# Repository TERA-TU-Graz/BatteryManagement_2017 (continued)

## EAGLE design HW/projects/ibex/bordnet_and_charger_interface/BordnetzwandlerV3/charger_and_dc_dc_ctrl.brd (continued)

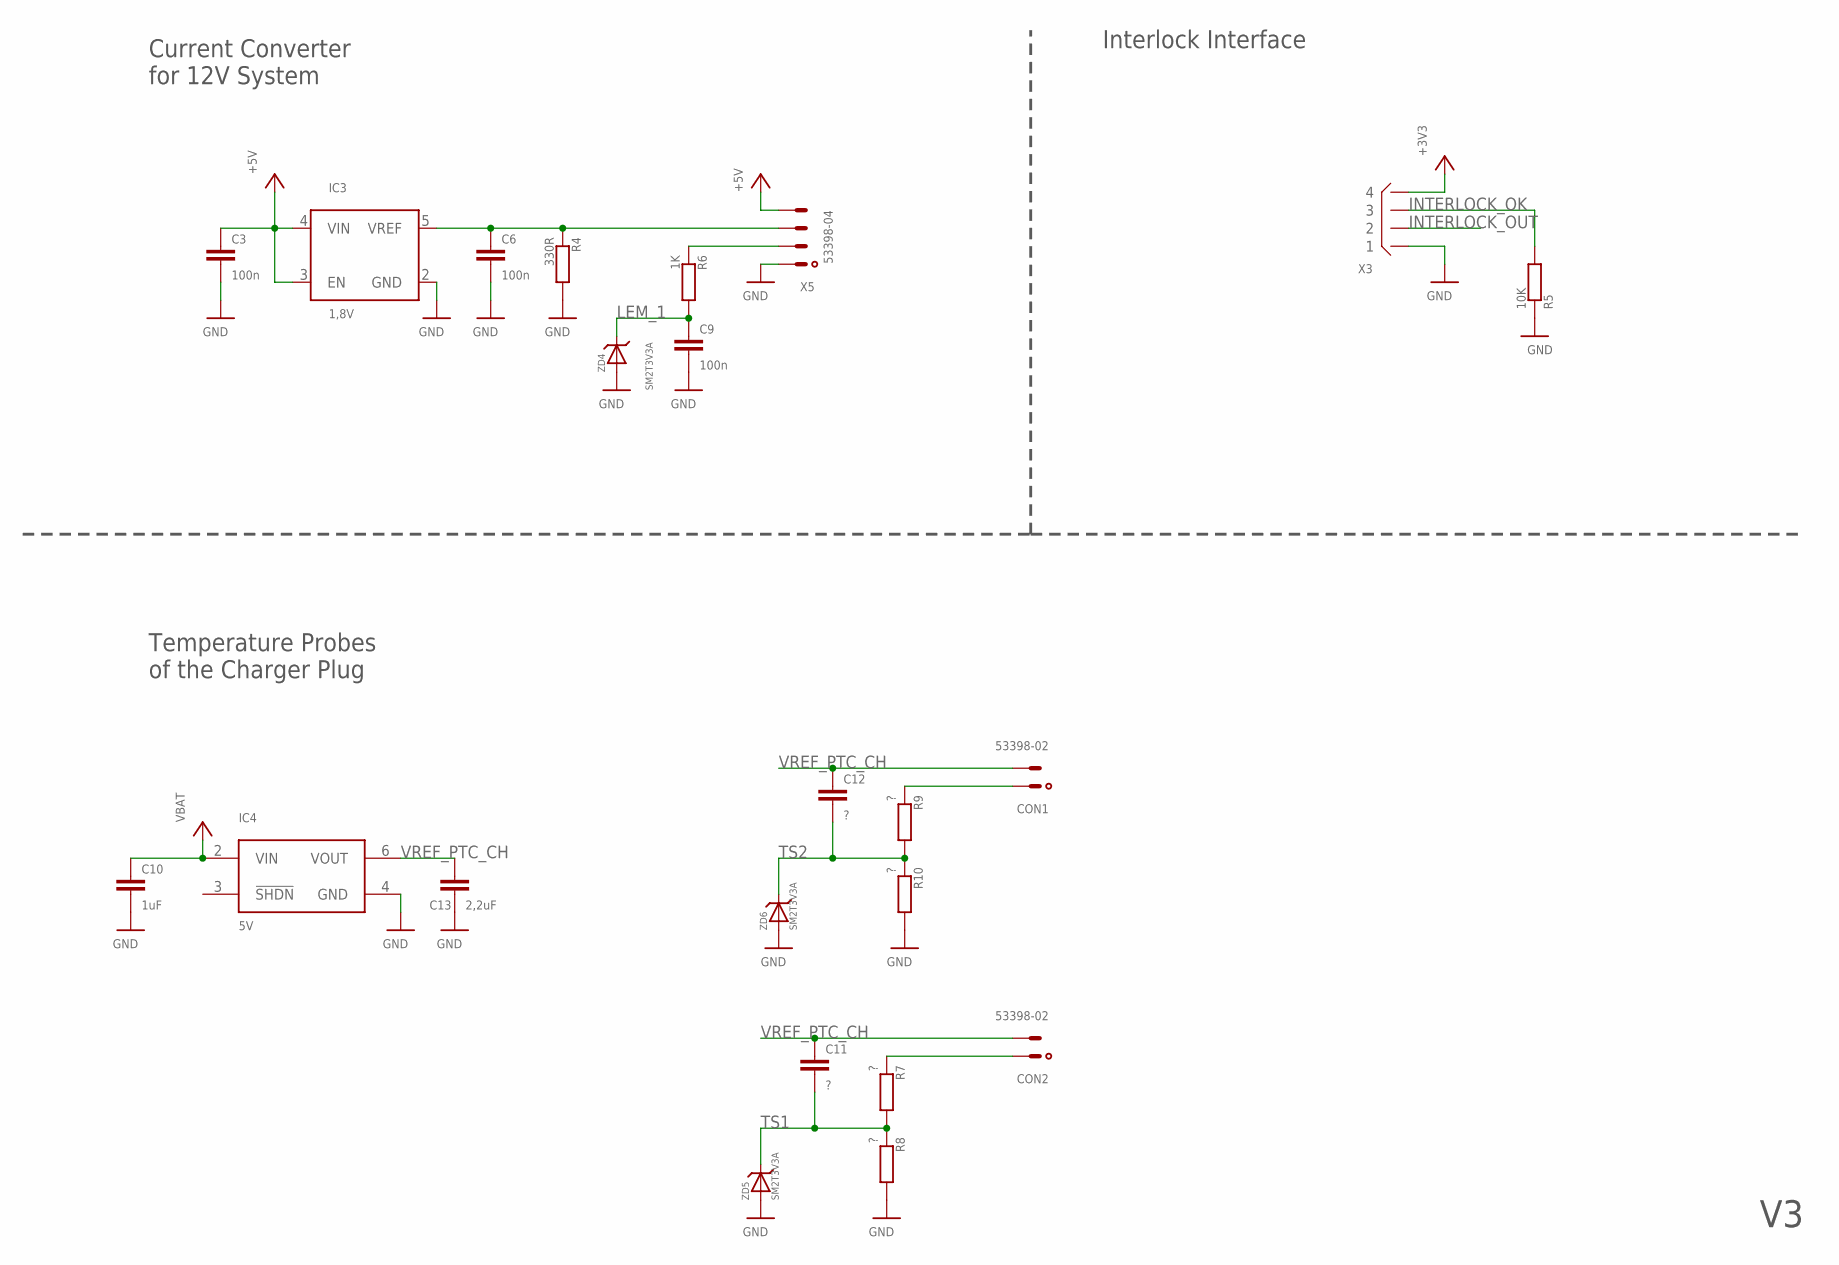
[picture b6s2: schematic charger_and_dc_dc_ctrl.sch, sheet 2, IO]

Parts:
C3, C6, C9: 100n; C0805
C10: 1uF; C0805
C11, C12: ?; C0805
C13: 2,2uF; C0805
CON1, CON2: 53398-02
IC3: 1,8V; SOT23-5L
IC4: 5V; SO08
R4: 330R; R0805
R5: 10K; R0603
R6: 1K; R0805
R7, R8, R9, R10: ?; R0805
X3: B4B-XH
X5: 53398-04
ZD4, ZD5, ZD6: SM2T3V3A

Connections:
+3V3: X3.P$4 (4); also elsewhere on the board
+5V: C3.1, IC3.3 (EN), IC3.4 (VIN), X5.4; also elsewhere on the board
GND: C3.2, C6.2, C9.2, C10.2, C13.2, IC3.2 (GND), IC4.4 (GND), R4.2, R5.1, R8.2, R10.2, X3.P$1 (1), X5.1, ZD4.P$1, ZD4.P$11, ZD5.P$1, ZD5.P$11, ZD6.P$1, ZD6.P$11; also elsewhere on the board
INTERLOCK_OK: R5.2, X3.P$3 (3); also elsewhere on the board
INTERLOCK_OUT: X3.P$2 (2); also elsewhere on the board
LEM_1: C9.1, R6.2, ZD4.P$2; also elsewhere on the board
unnamed: R6.1, X5.2
unnamed: CON1.1, R9.1
unnamed: C6.1, IC3.5 (VREF), R4.1, X5.3
unnamed: CON2.1, R7.1
TS1: C11.2, R7.2, R8.1, ZD5.P$2; also elsewhere on the board
TS2: C12.2, R9.2, R10.1, ZD6.P$2; also elsewhere on the board
VBAT: C10.1, IC4.2 (VIN); also elsewhere on the board
VREF_PTC_CH: C11.1, C12.1, C13.1, CON1.2, CON2.2, IC4.6 (VOUT)

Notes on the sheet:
Current Converter for 12V System
Temperature Probes of the Charger Plug
Interlock Interface

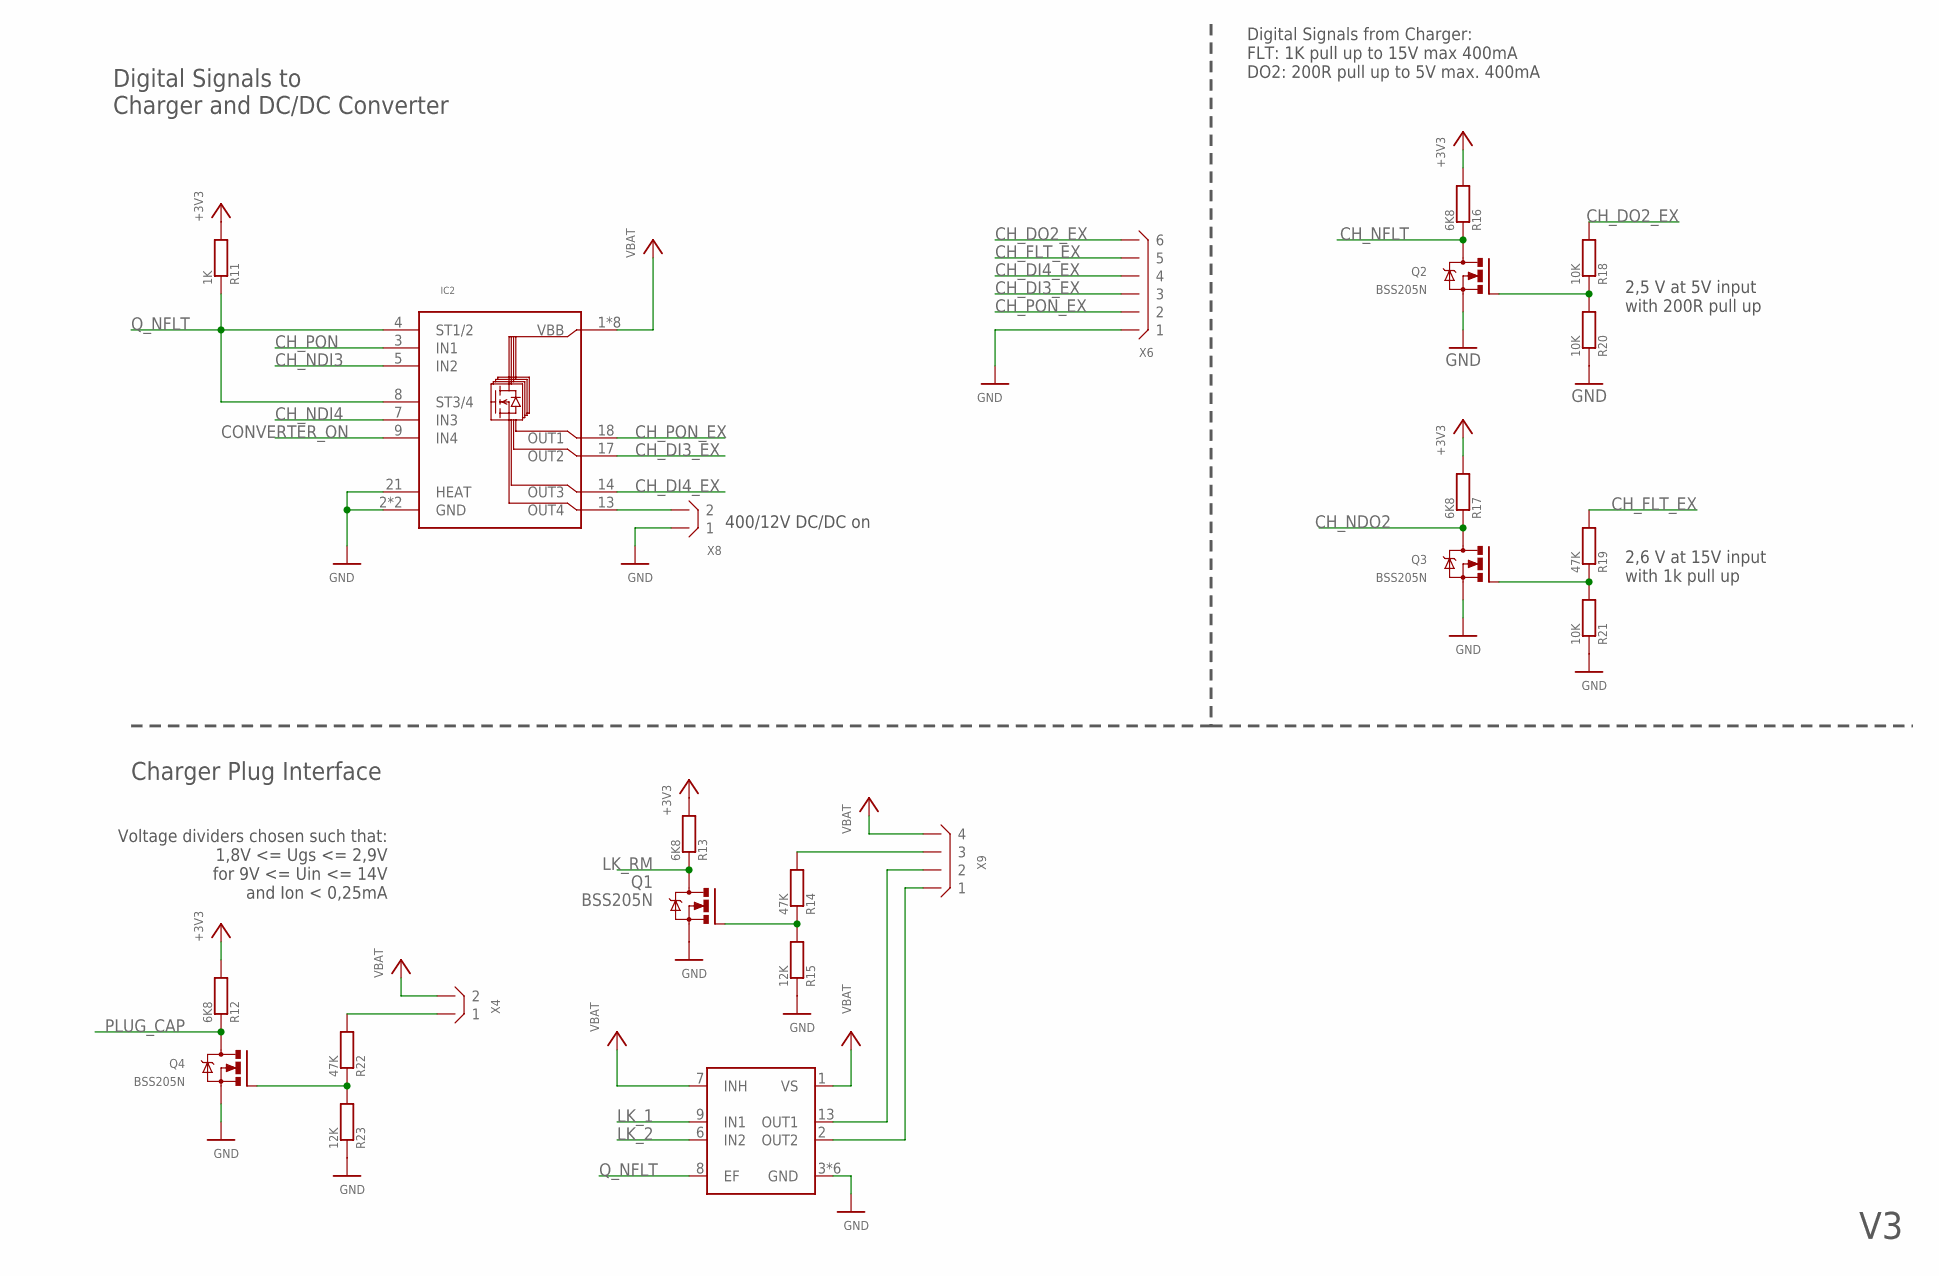
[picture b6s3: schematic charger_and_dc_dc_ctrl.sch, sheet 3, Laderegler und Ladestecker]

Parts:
IC2: BTS716G-NEWM; INF-PG-DSO-20-30_M_1PRIMARY
IC6: TLE4207GN; INF-PG-DSO-14-22_N_1PRIMARY
Q1, Q2, Q3, Q4: BSS205N; SOT23
R11: 1K; R0603
R12, R16, R17: 6K8; R0603
R13: 6K8; R0805
R14: 47K; R0805
R15: 12K; R0805
R18, R20, R21: 10K; R0603
R19, R22: 47K; R0603
R23: 12K; R0603
X4, X8: B2B-XH
X6: B6B-XH
X9: B4B-XH

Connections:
+3V3: R11.2, R12.2, R13.2, R16.2, R17.2; also elsewhere on the board
CH_DI3_EX: IC2.17 (OUT2), X6.P$3 (3)
CH_DI4_EX: IC2.14 (OUT3), X6.P$4 (4)
CH_DO2_EX: R18.2, X6.P$6 (6)
CH_FLT_EX: R19.2, X6.P$5 (5)
CH_NDI3: IC2.5 (IN2); also elsewhere on the board
CH_NDI4: IC2.7 (IN3); also elsewhere on the board
CH_NDO2: Q3.3 (D), R17.1; also elsewhere on the board
CH_NFLT: Q2.3 (D), R16.1; also elsewhere on the board
CH_PON: IC2.3 (IN1); also elsewhere on the board
CH_PON_EX: IC2.18 (OUT1), X6.P$2 (2)
CONVERTER_ON: IC2.9 (IN4); also elsewhere on the board
GND: IC2.2 (GND), IC2.6 (GND), IC2.21 (HEAT), IC6.3 (GND), IC6.4 (GND), IC6.5 (GND), IC6.10 (GND), IC6.11 (GND), IC6.12 (GND), Q1.2 (S), Q2.2 (S), Q3.2 (S), Q4.2 (S), R15.1, R20.1, R21.1, R23.1, X6.P$1 (1), X8.P$1 (1); also elsewhere on the board
LK_1: IC6.9 (IN1); also elsewhere on the board
LK_2: IC6.6 (IN2); also elsewhere on the board
LK_RM: Q1.3 (D), R13.1; also elsewhere on the board
unnamed: IC2.13 (OUT4), X8.P$2 (2)
unnamed: Q4.1 (G), R22.1, R23.2
unnamed: R22.2, X4.P$1 (1)
unnamed: Q3.1 (G), R19.1, R21.2
unnamed: Q1.1 (G), R14.1, R15.2
unnamed: R14.2, X9.P$3 (3)
unnamed: IC6.13 (OUT1), X9.P$2 (2)
unnamed: IC6.2 (OUT2), X9.P$1 (1)
unnamed: Q2.1 (G), R18.1, R20.2
PLUG_CAP: Q4.3 (D), R12.1; also elsewhere on the board
Q_NFLT: IC2.4 (ST1/2), IC2.8 (ST3/4), IC6.8 (EF), R11.1; also elsewhere on the board
VBAT: IC2.1 (VBB), IC2.10 (VBB), IC2.11 (VBB), IC2.12 (VBB), IC2.15 (VBB), IC2.16 (VBB), IC2.19 (VBB), IC2.20 (VBB), IC6.1 (VS), IC6.7 (INH), X4.P$2 (2), X9.P$4 (4); also elsewhere on the board

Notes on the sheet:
Voltage dividers chosen such that: 1,8V <= Ugs <= 2,9V for 9V <= Uin <= 14V and Ion < 0,25mA
Digital Signals from Charger: FLT: 1K pull up to 15V max 400mA DO2: 200R pull up to 5V max. 400mA
2,6 V at 15V input with 1k pull up
2,5 V at 5V input with 200R pull up
400/12V DC/DC on
Charger Plug Interface
Digital Signals to Charger and DC/DC Converter

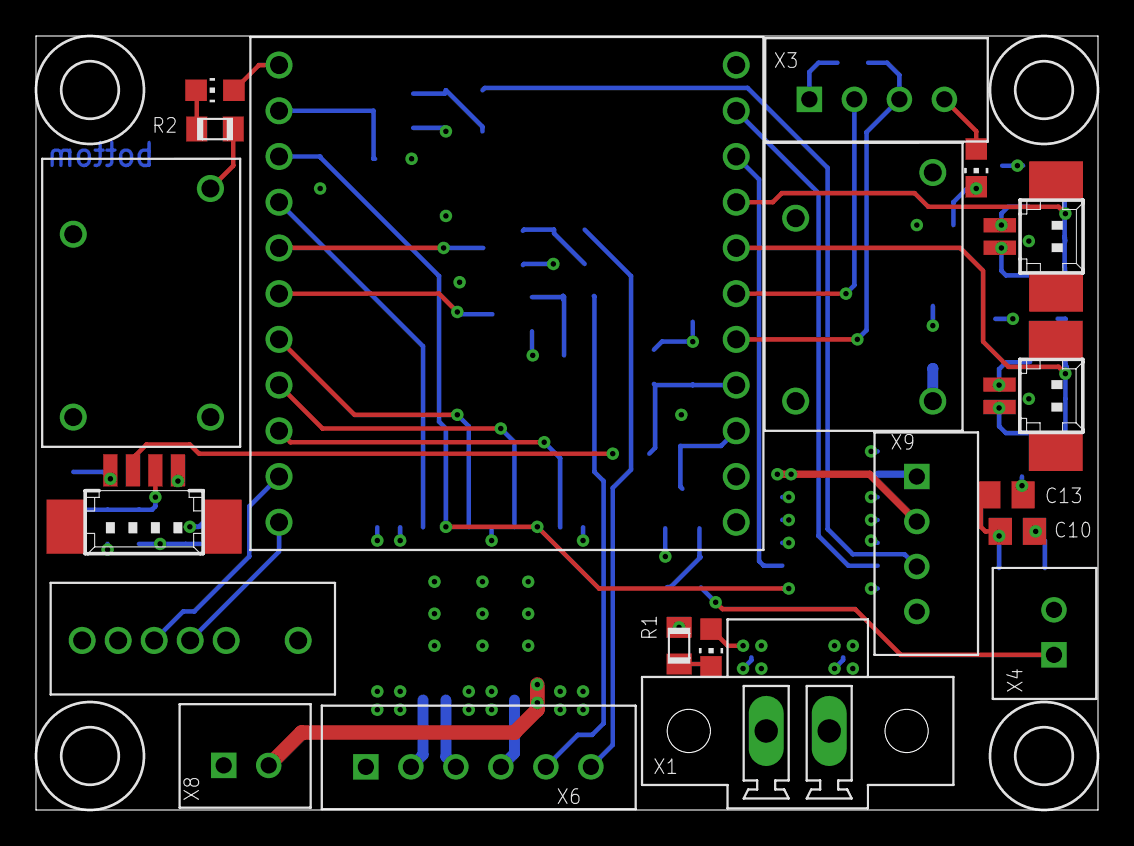
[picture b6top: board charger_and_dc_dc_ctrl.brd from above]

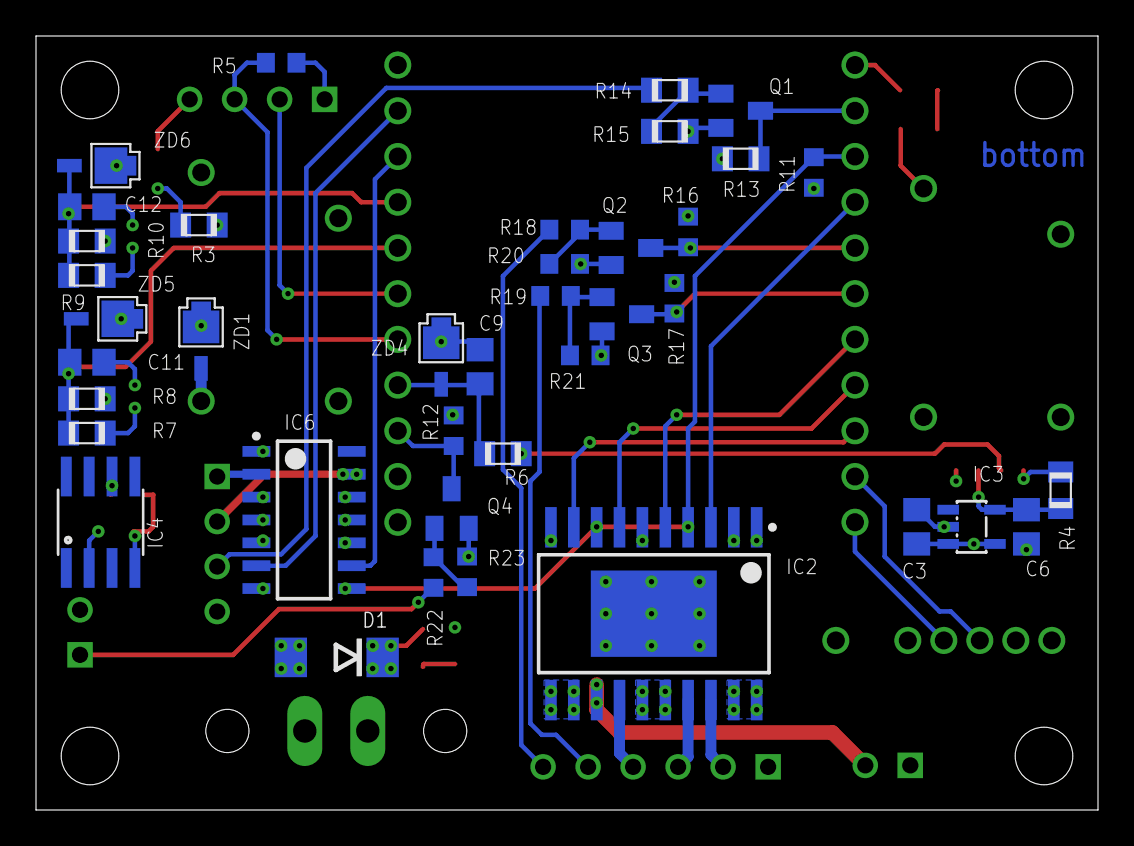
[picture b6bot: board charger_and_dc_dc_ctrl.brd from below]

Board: 4 copper layers, 59.0 x 43.0 mm, 63 parts (39 on the bottom side), 44 nets.

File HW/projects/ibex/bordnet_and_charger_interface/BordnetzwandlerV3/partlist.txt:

Partlist

Exported from charger_and_dc_dc_ctrl.sch at 25.10.15 21:49

EAGLE Version 6.6.0 Copyright (c) 1988-2014 CadSoft

Assembly variant: 

Part     Value                        Device                       Package                     Library     Sheet

C3       100n                         C-EUC0805                    C0805                       rcl         2
C6       100n                         C-EUC0805                    C0805                       rcl         2
C9       100n                         C-EUC0805                    C0805                       rcl         2
C10      1uF                          C-EUC0805                    C0805                       rcl         2
C11      ?                            C-EUC0805                    C0805                       rcl         2
C12      ?                            C-EUC0805                    C0805                       rcl         2
C13      2,2uF                        C-EUC0805                    C0805                       rcl         2
CANIO_1  STM32F103XX_CAN-IO-EXPANDERC STM32F103XX_CAN-IO-EXPANDERC STM32F103XX_CANIO-EXPANDER3 tera-boards 1
CON1     53398-02                     53398-02                     53398-02                    con-molex   2
CON2     53398-02                     53398-02                     53398-02                    con-molex   2
D1       18V                          DIODE-DO214AA                DO214AA                     diode       1
IC2      BTS716G-NEWM                 BTS716G-NEWM                 INF-PG-DSO-20-30_M_1PRIMARY infineon    3
IC3      1,8V                         LM4132L                      SOT23-5L                    ti          2
IC4      5V                           LT1461                       SO08                        linear      2
IC6      TLE4207GN                    TLE4207GN                    INF-PG-DSO-14-22_N_1PRIMARY infineon    3
LED1     green                        LEDCHIP-LED0805              CHIP-LED0805                led         1
LED2     green                        LEDCHIP-LED0805              CHIP-LED0805                led         1
LED3     green                        LEDCHIP-LED0805              CHIP-LED0805                led         1
Q1       BSS205N                      BSS205N                      SOT23                       infineon    3
Q2       BSS205N                      BSS205N                      SOT23                       infineon    3
Q3       BSS205N                      BSS205N                      SOT23                       infineon    3
Q4       BSS205N                      BSS205N                      SOT23                       infineon    3
R1       12K                          R                            R0805                       useful      1
R2       5K6                          R                            R0805                       useful      1
R3       3K3                          R                            R0805                       useful      1
R4       330R                         R                            R0805                       useful      2
R5       10K                          R0603                        R0603                       useful      2
R6       1K                           R                            R0805                       useful      2
R7       ?                            R                            R0805                       useful      2
R8       ?                            R                            R0805                       useful      2
R9       ?                            R                            R0805                       useful      2
R10      ?                            R                            R0805                       useful      2
R11      1K                           R0603                        R0603                       useful      3
R12      6K8                          R0603                        R0603                       useful      3
R13      6K8                          R                            R0805                       useful      3
R14      47K                          R                            R0805                       useful      3
R15      12K                          R                            R0805                       useful      3
R16      6K8                          R0603                        R0603                       useful      3
R17      6K8                          R0603                        R0603                       useful      3
R18      10K                          R0603                        R0603                       useful      3
R19      47K                          R0603                        R0603                       useful      3
R20      10K                          R0603                        R0603                       useful      3
R21      10K                          R0603                        R0603                       useful      3
R22      47K                          R0603                        R0603                       useful      3
R23      12K                          R0603                        R0603                       useful      3
TB1      MAX16956_STEPDOWN6           MAX16956_STEPDOWN6           MAX16956_STEPDOWN6          tera-boards 1
TB2      MAX16956_STEPDOWN6           MAX16956_STEPDOWN6           MAX16956_STEPDOWN6          tera-boards 1
X1       MCV1,5/2-GF-3,5              MCV1,5/2-GF-3,5              MCV1,5/2-GF-3,5             con-phoenix 1
X2       CIOC_4-1-FV-A_CAN-BELEGUNG   CIOC_4-1-FV-A_CAN-BELEGUNG   CIOC_4-1-FV                 con-phoenix 1
X3       B4B-XH                       B4B-XH                       B4B-XH                      con-jst-xh  2
X4       B2B-XH                       B2B-XH                       B2B-XH                      con-jst-xh  3
X5       53398-04                     53398-04                     53398-04                    con-molex   2
X6       B6B-XH                       B6B-XH                       B6B-XH                      con-jst-xh  3
X8       B2B-XH                       B2B-XH                       B2B-XH                      con-jst-xh  3
X9       B4B-XH                       B4B-XH                       B4B-XH                      con-jst-xh  3
ZD1      SM2T3V3A                     SM2T3V3A                     SM2T3V3A                    st          1
ZD4      SM2T3V3A                     SM2T3V3A                     SM2T3V3A                    st          2
ZD5      SM2T3V3A                     SM2T3V3A                     SM2T3V3A                    st          2
ZD6      SM2T3V3A                     SM2T3V3A                     SM2T3V3A                    st          2

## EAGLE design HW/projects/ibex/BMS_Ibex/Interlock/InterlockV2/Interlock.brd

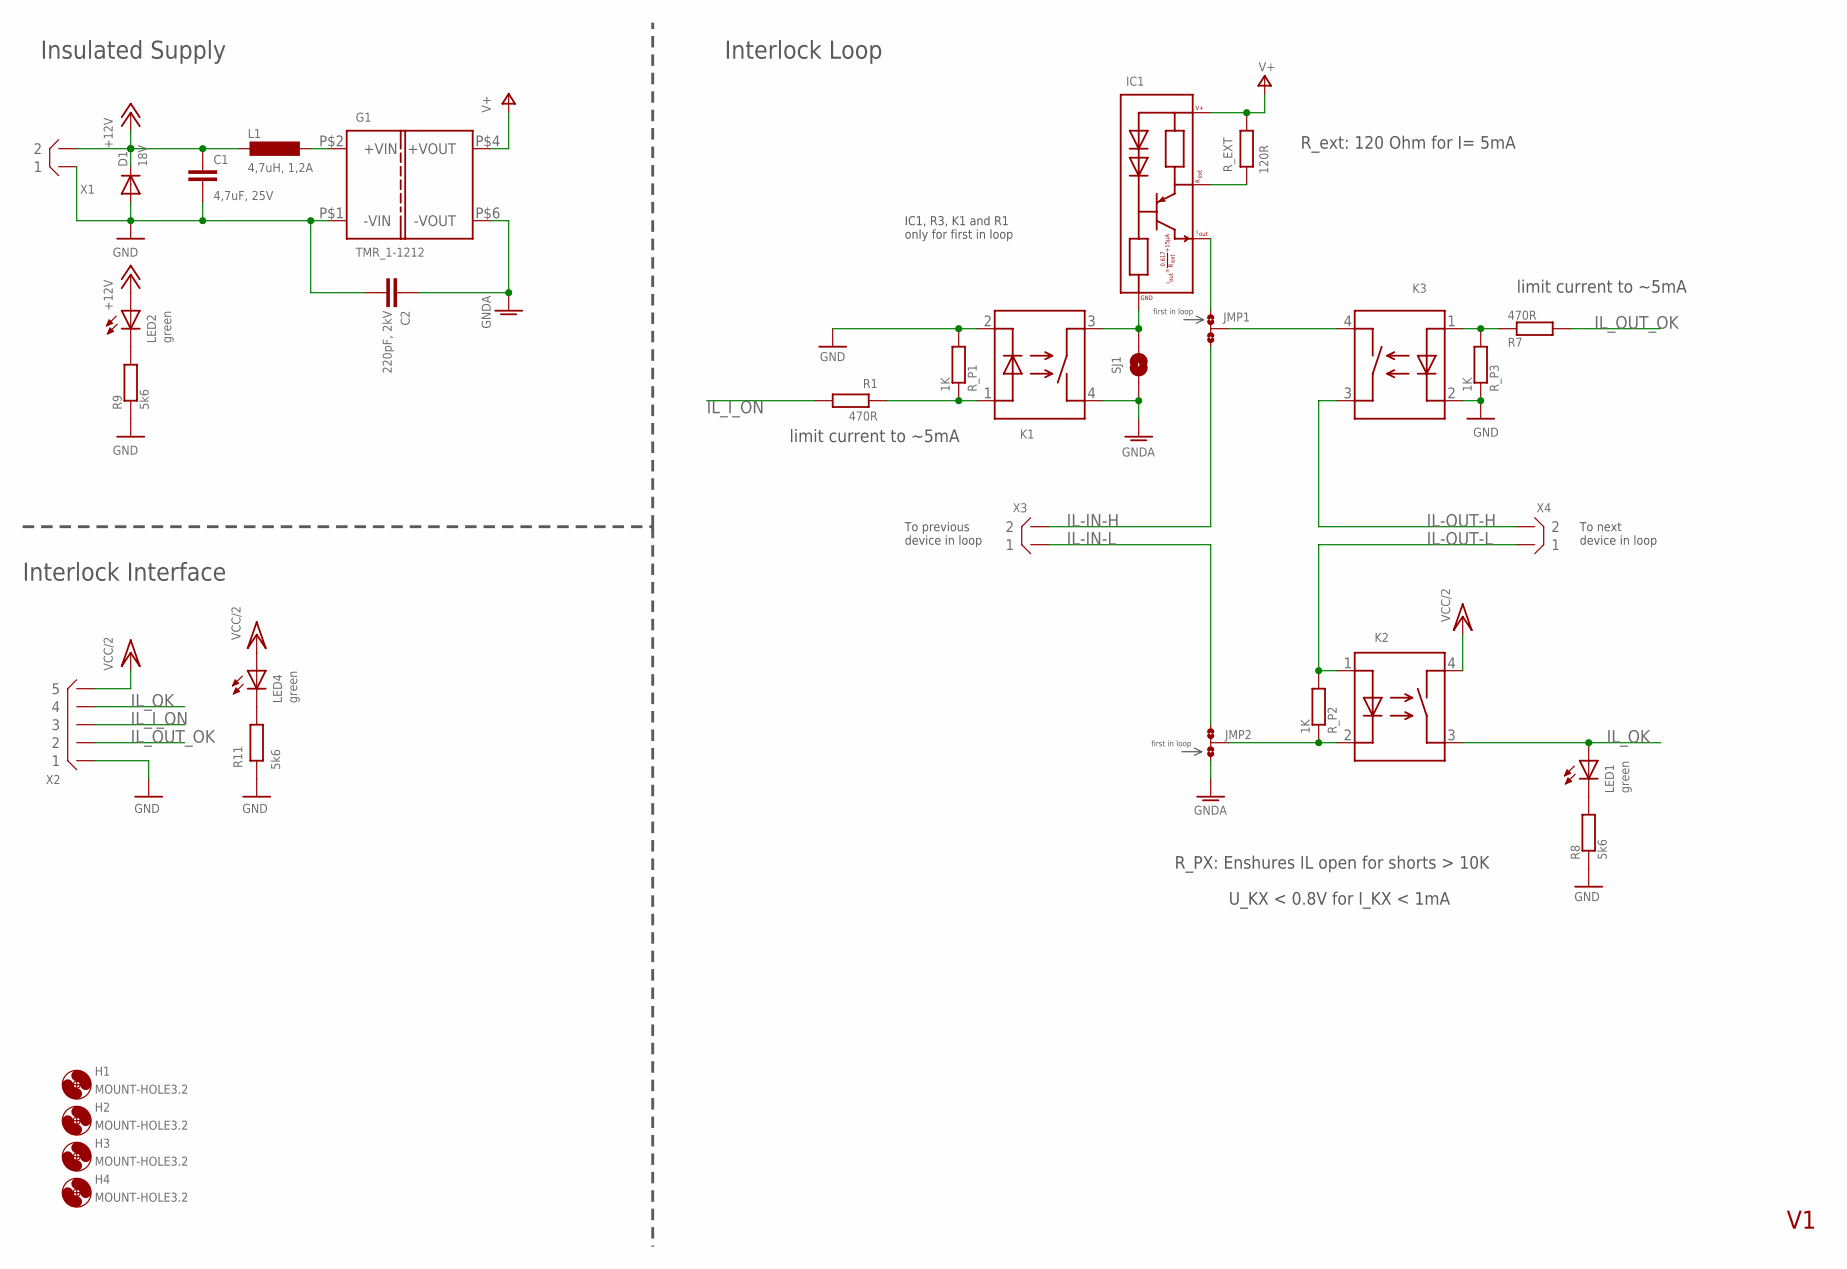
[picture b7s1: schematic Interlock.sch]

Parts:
C1: 4,7uF, 25V; C0805
C2: 220pF, 2kV; C1210_HV
D1: 18V; DO214AA
G1: TMR_1-1212; TMR_1-??1?
H1, H2, H3, H4: MOUNT-HOLE3.2; 3,2
IC1: PSSI2021SAY; SOT353
JMP1, JMP2: 0R-JUMPA; A0R-JMP
K1, K2, K3: ASSR-1218; SO-4
L1: 4,7uH, 1,2A; L3225M
LED1, LED2, LED4: green; CHIPLED_0805
R1, R7: 470R; R0805
R8, R9, R11: 5k6; R0805
R_EXT: 120R; R0805
R_P1, R_P2, R_P3: 1K; R0603
SJ1: SOLDERJUMPERNO; SJ_2S-NO
X1, X3, X4: B2B-XH
X2: B5B-XH

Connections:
+12V: C1.1, D1.C, L1.2, LED2.A, X1.P$2 (2)
GND: C1.2, C2.P$1 (1), D1.A, G1.P$1 (-VIN), K1.2 (I-), K3.2 (I-), R8.1, R9.1, R11.1, R_P1.2, R_P3.1, X1.P$1 (1), X2.P$1 (1)
GNDA: C2.P$2 (2), G1.P$6 (-VOUT), JMP2.1, K1.4 (O1), SJ1.1
IL-IN-H: JMP1.3, X3.P$2 (2)
IL-IN-L: JMP2.3, X3.P$1 (1)
IL-OUT-H: K3.3 (O2), X4.P$2 (2)
IL-OUT-L: K2.1 (I+), R_P2.2, X4.P$1 (1)
IL_I_ON: R1.2, X2.P$3 (3)
IL_OK: K2.3 (O2), LED1.A, X2.P$4 (4)
IL_OUT_OK: R7.2, X2.P$2 (2)
unnamed: IC1.4 (REXT), R_EXT.1
unnamed: G1.P$2 (+VIN), L1.1
unnamed: K3.1 (I+), R7.1, R_P3.2
unnamed: JMP1.2, K3.4 (O1)
unnamed: IC1.2 (IOUT), JMP1.1
unnamed: JMP2.2, K2.2 (I-), R_P2.1
unnamed: IC1.3 (GND), K1.3 (O2), SJ1.2
unnamed: LED2.C, R9.2
unnamed: K1.1 (I+), R1.1, R_P1.1
unnamed: LED4.C, R11.2
unnamed: LED1.C, R8.2
V+: G1.P$4 (+VOUT), IC1.5 (VSS), R_EXT.2
VCC/2: K2.4 (O1), LED4.A, X2.P$5 (5)

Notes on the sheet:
R_ext: 120 Ohm for I= 5mA
limit current to ~5mA
Insulated Supply
Interlock Loop
Interlock Interface
IC1, R3, K1 and R1 only for first in loop
first in loop
To previous device in loop
To next device in loop
U_KX < 0.8V for I_KX < 1mA
R_PX: Enshures IL open for shorts > 10K

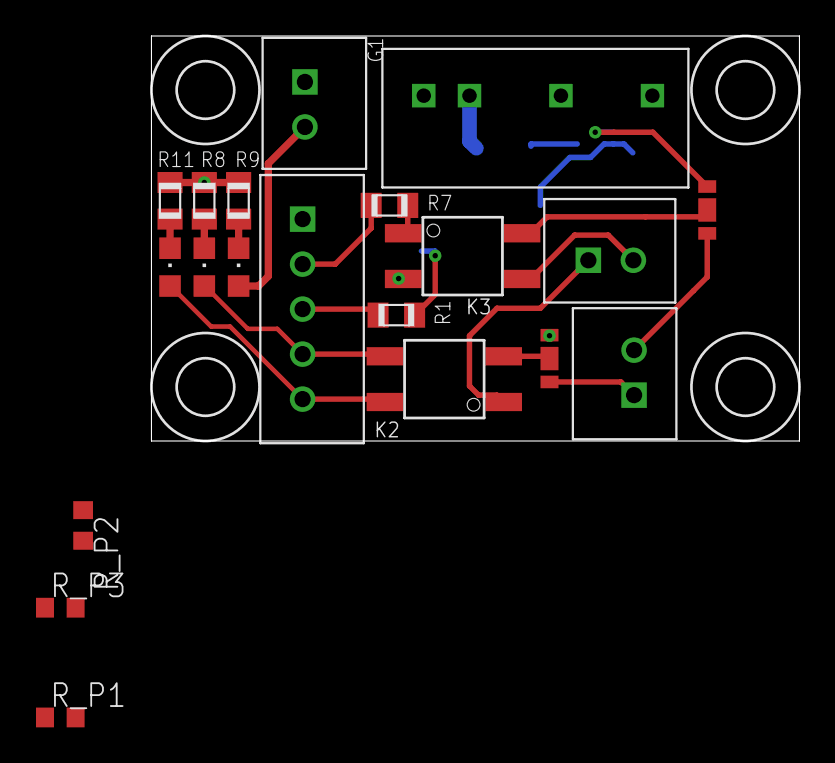
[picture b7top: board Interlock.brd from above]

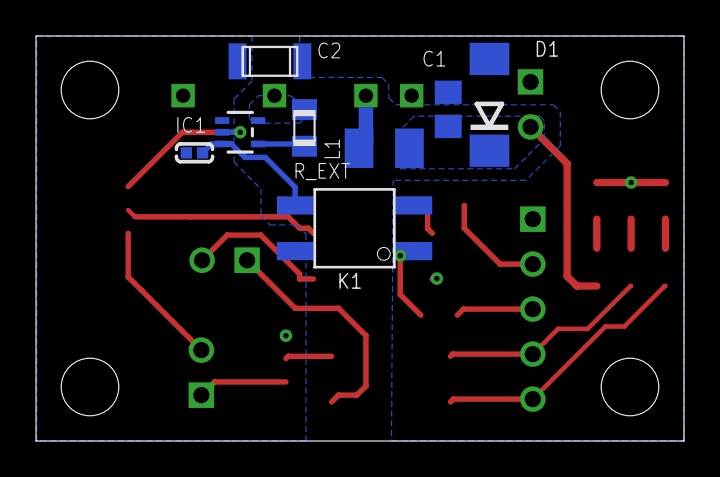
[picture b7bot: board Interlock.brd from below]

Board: 4 copper layers, 36.0 x 22.5 mm, 32 parts (8 on the bottom side), 23 nets.

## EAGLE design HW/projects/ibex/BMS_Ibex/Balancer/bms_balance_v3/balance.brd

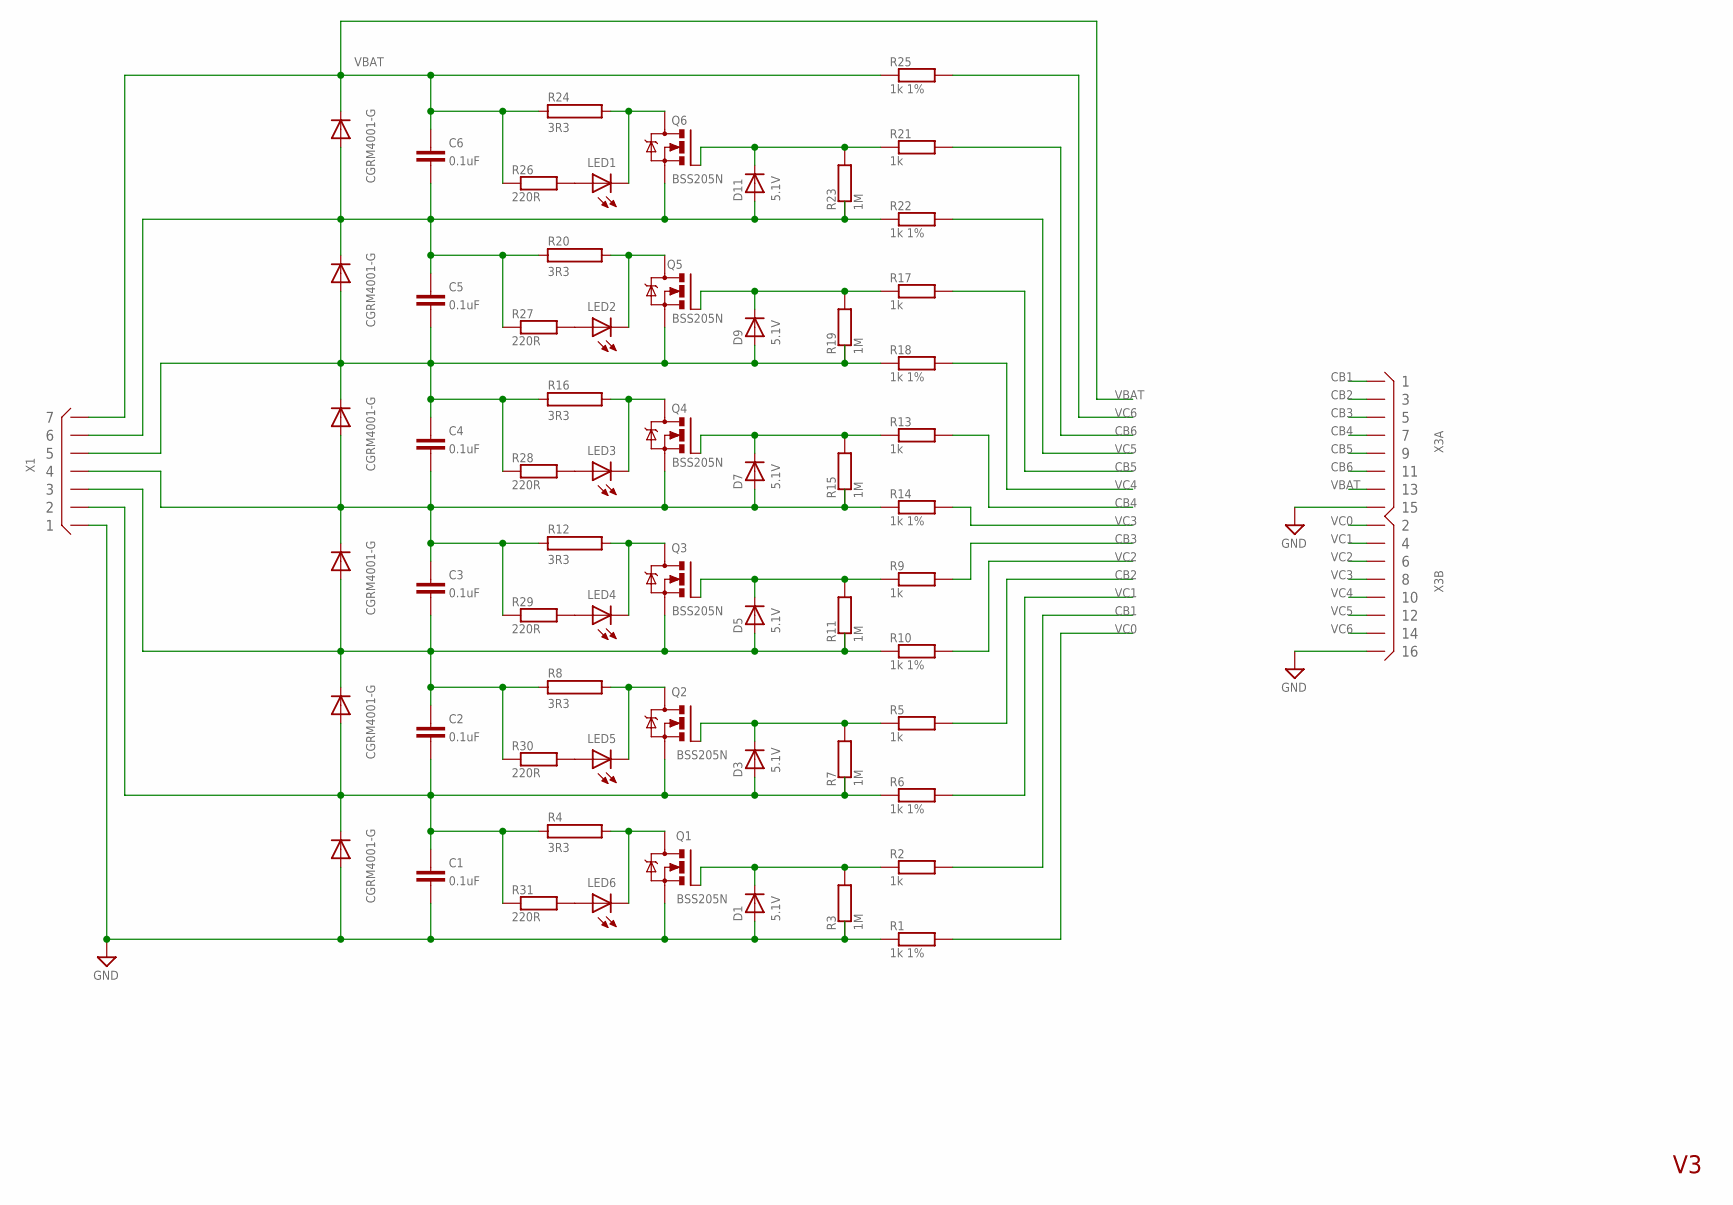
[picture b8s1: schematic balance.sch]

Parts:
C1, C2, C3, C4, C5, C6: 0.1uF; C0805
D1, D3, D5, D7, D9, D11: 5.1V; SOD-323
D2, D4, D6, D8, D10, D12: CGRM4001-G; SOD-123_MINI-SMA
LED1, LED2, LED3, LED4, LED5, LED6: LEDCHIP-LED0805; CHIP-LED0805
Q1, Q2, Q3, Q4, Q5, Q6: BSS205N; SOT23
R1, R6, R10, R14, R18, R22, R25: 1k 1%; R0805
R2, R5, R9, R13, R17, R21: 1k; R0805
R3, R7, R11, R15, R19, R23: 1M; R0805
R4, R8, R12, R16, R20, R24: 3R3; HS15
R26, R27, R28, R29, R30, R31: 220R; R0805
X1: B7B-XH
X3: X08X2DR; X16R-DIL

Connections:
1: LED6.C, Q1.3 (D), R4.2
2: C1.2, C2.1, D2.C, D3.2 (A), D4.A, Q2.2 (S), R4.1, R6.1, R7.1, R31.1, X1.P$2 (2)
3: LED5.C, Q2.3 (D), R8.2
4: C2.2, C3.1, D4.C, D5.2 (A), D6.A, Q3.2 (S), R8.1, R10.1, R11.1, R30.1, X1.P$3 (3)
5: LED4.C, Q3.3 (D), R12.2
6: C3.2, C4.1, D6.C, D7.2 (A), D8.A, Q4.2 (S), R12.1, R14.1, R15.1, R29.1, X1.P$4 (4)
7: LED3.C, Q4.3 (D), R16.2
8: C4.2, C5.1, D8.C, D9.2 (A), D10.A, Q5.2 (S), R16.1, R18.1, R19.1, R28.1, X1.P$5 (5)
9: LED2.C, Q5.3 (D), R20.2
10: C5.2, C6.1, D10.C, D11.2 (A), D12.A, Q6.2 (S), R20.1, R22.1, R23.1, R27.1, X1.P$6 (6)
11: LED1.C, Q6.3 (D), R24.2
CB1: R2.2, X3.1
CB2: R5.2, X3.3
CB3: R9.2, X3.5
CB4: R13.2, X3.7
CB5: R17.2, X3.9
CB6: R21.2, X3.11
GND: C1.1, D1.2 (A), D2.A, Q1.2 (S), R1.1, R3.1, X1.P$1 (1), X3.15, X3.16
unnamed: D1.1 (C), Q1.1 (G), R2.1, R3.2
unnamed: D3.1 (C), Q2.1 (G), R5.1, R7.2
unnamed: LED1.A, R26.2
unnamed: LED2.A, R27.2
unnamed: LED3.A, R28.2
unnamed: D5.1 (C), Q3.1 (G), R9.1, R11.2
unnamed: LED4.A, R29.2
unnamed: LED5.A, R30.2
unnamed: LED6.A, R31.2
unnamed: D7.1 (C), Q4.1 (G), R13.1, R15.2
unnamed: D9.1 (C), Q5.1 (G), R17.1, R19.2
unnamed: D11.1 (C), Q6.1 (G), R21.1, R23.2
VBAT: C6.2, D12.C, R24.1, R25.1, R26.1, X1.P$7 (7), X3.13
VC0: R1.2, X3.2
VC1: R6.2, X3.4
VC2: R10.2, X3.6
VC3: R14.2, X3.8
VC4: R18.2, X3.10
VC5: R22.2, X3.12
VC6: R25.2, X3.14

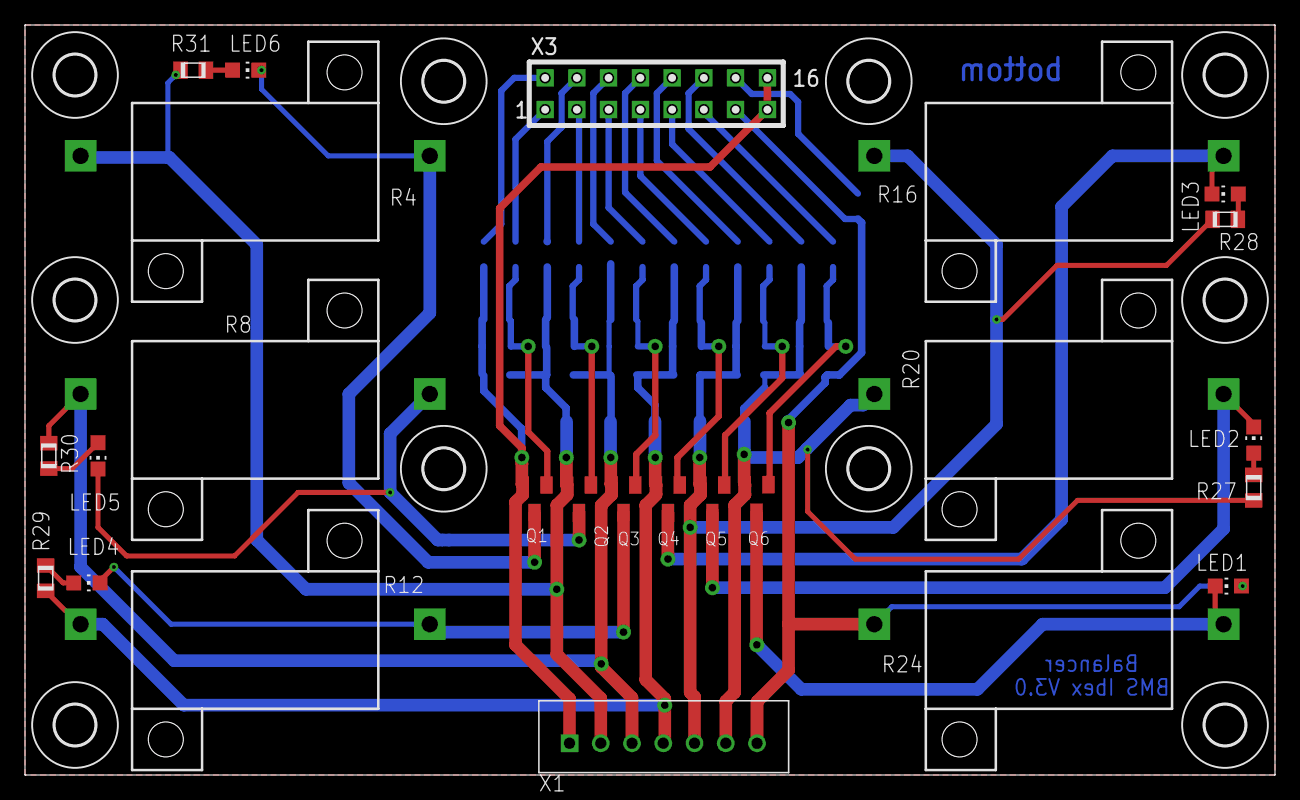
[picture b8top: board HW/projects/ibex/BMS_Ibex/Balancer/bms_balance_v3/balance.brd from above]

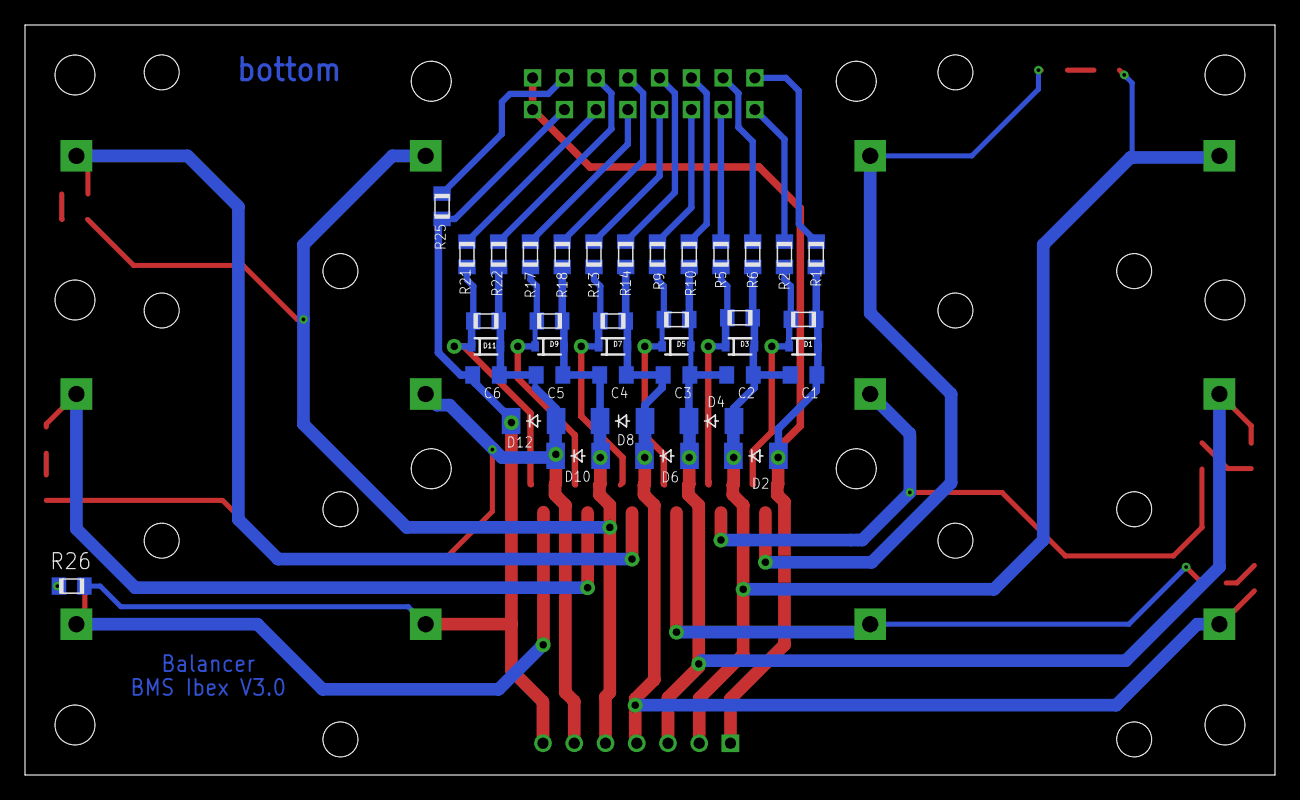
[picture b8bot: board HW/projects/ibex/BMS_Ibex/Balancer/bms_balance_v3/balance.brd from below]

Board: 4 copper layers, 100.0 x 60.0 mm, 73 parts (38 on the bottom side), 38 nets.

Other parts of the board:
U$1, U$2, U$3, U$4, U$5, U$6, U$7, U$8, U$9, U$10: 3,2

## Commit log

2017-08-10 Initial commit software.
2017-08-10 Adding kicad libs
2017-08-10 Adding PCB files
2017-08-10 Adding license file
2018-10-28 Update github repo with designs for fennek 2018
2018-10-28 Update submodule for libraries
2018-10-28 update submodule container for general projects
2018-10-28 Sync ibex bms with tera local
